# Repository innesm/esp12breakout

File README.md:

# esp12breakout

A single-sided PCB breakout board for ESP12 modules.

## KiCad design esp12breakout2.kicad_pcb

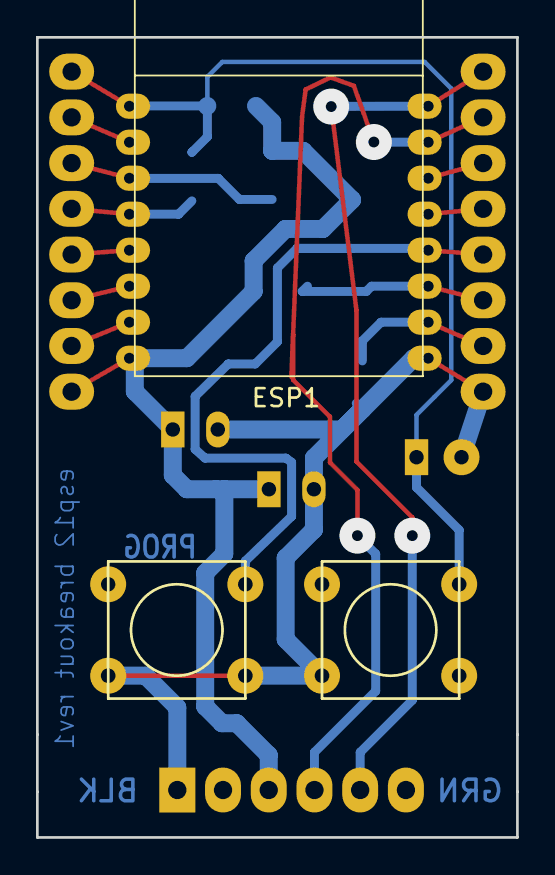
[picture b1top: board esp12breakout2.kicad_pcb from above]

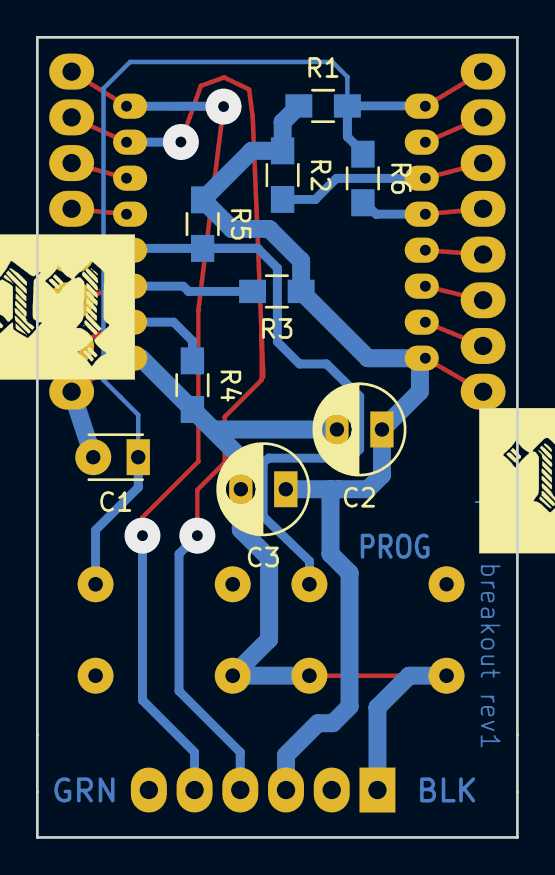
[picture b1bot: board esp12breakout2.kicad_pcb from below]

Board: 2 copper layers, 26.7 x 44.5 mm, 15 parts (9 on the bottom side), 16 nets.

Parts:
C1: 100nF; C_Disc_D3_P2.5
C2: 100uf; C_Radial_D5_L11_P2.5
C3: 10uf; C_Radial_D5_L11_P2.5
ESP1: esp12
P1, P2: CONN_01X08; Pin_Header_Straight_1x08
P3: FT232_3V3; Pin_Header_Straight_1x06
R1, R2, R3, R4, R5: 10K; R_0805_HandSoldering
R6: R; R_0805_HandSoldering
SW1: reset; SW_PUSH_SMALL
SW2: program; SW_PUSH_SMALL

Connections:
+3V3: C2.1, C3.1, ESP1.8, P1.1, P3.3, R1.1, R2.1, R3.1, R5.1
/ADC: ESP1.2, P1.7
/D0: ESP1.12, P2.5, R5.2, SW2.1
/D2: ESP1.11, P2.6, R3.2
/D15: ESP1.10, P2.7, R4.1
/D16: ESP1.4, P1.5, R6.2
/EN: ESP1.3, P1.6, R2.2
/MISO: ESP1.6, P1.3
/MOSI: ESP1.7, P1.2
/RESET: C1.1, ESP1.1, P1.8, R1.2, R6.1, SW1.1
/RX: ESP1.15, P2.2, P3.4
/SCK: ESP1.5, P1.4
/SCL: ESP1.14, P2.3
/SDA: ESP1.13, P2.4
/TX: ESP1.16, P2.1, P3.5
GND: C1.2, C2.2, C3.2, ESP1.9, P2.8, P3.1, R4.2, SW1.2, SW2.2

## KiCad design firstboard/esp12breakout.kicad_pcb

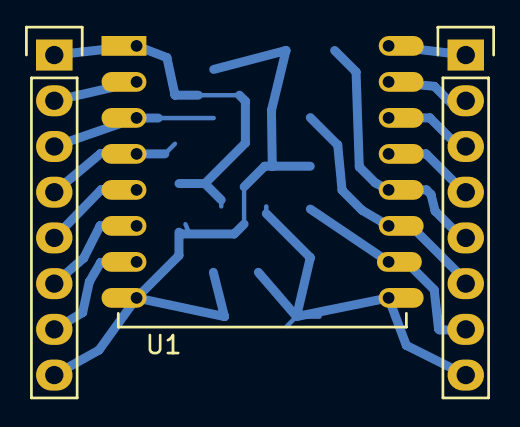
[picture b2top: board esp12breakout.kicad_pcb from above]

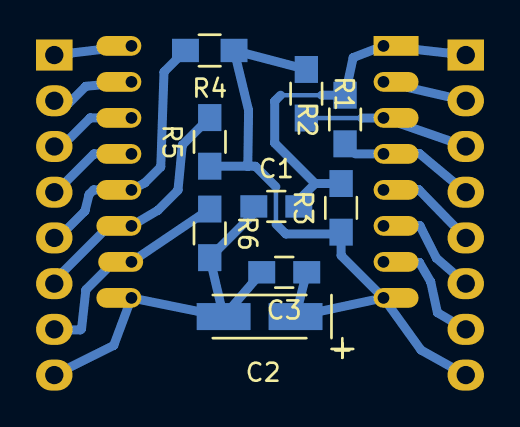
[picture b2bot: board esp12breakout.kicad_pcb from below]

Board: 2 copper layers, 12 parts (9 on the bottom side), 16 nets.

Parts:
C1, C3: 100nF; C_0805_HandSoldering
C2: 10uF; TantalC_SizeA_EIA-3216_HandSoldering
P1, P2: CONN_01X08; Pin_Header_Straight_1x08
R1, R3, R4, R5, R6: 10k; R_0805_HandSoldering
R2: 1k; R_0805_HandSoldering
U1: ESP-12

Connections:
+3V3: C2.1, C3.1, P1.8, R1.1, R3.1, R4.1, R5.1, U1.8
/ADC: P1.2, U1.2
/EN: P1.3, R1.2, U1.3
/GPIO0: P2.5, R4.2, U1.12
/GPIO2: P2.6, R5.2, U1.11
/GPIO4: P2.4, U1.13
/GPIO5: P2.3, U1.14
/GPIO12: P1.6, U1.6
/GPIO13: P1.7, U1.7
/GPIO14: P1.5, U1.5
/GPIO15: P2.7, R6.1, U1.10
/GPIO16: P1.4, R2.1, U1.4
/REST: C1.2, P1.1, R2.2, R3.2, U1.1
/RXD: P2.2, U1.15
/TXD: P2.1, U1.16
GND: C1.1, C2.2, C3.2, P2.8, R6.2, U1.9

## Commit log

2016-04-07 Add readme
2016-04-10 esp12 single sided pcb
2016-04-11 first board attempt.
2016-04-11 move
